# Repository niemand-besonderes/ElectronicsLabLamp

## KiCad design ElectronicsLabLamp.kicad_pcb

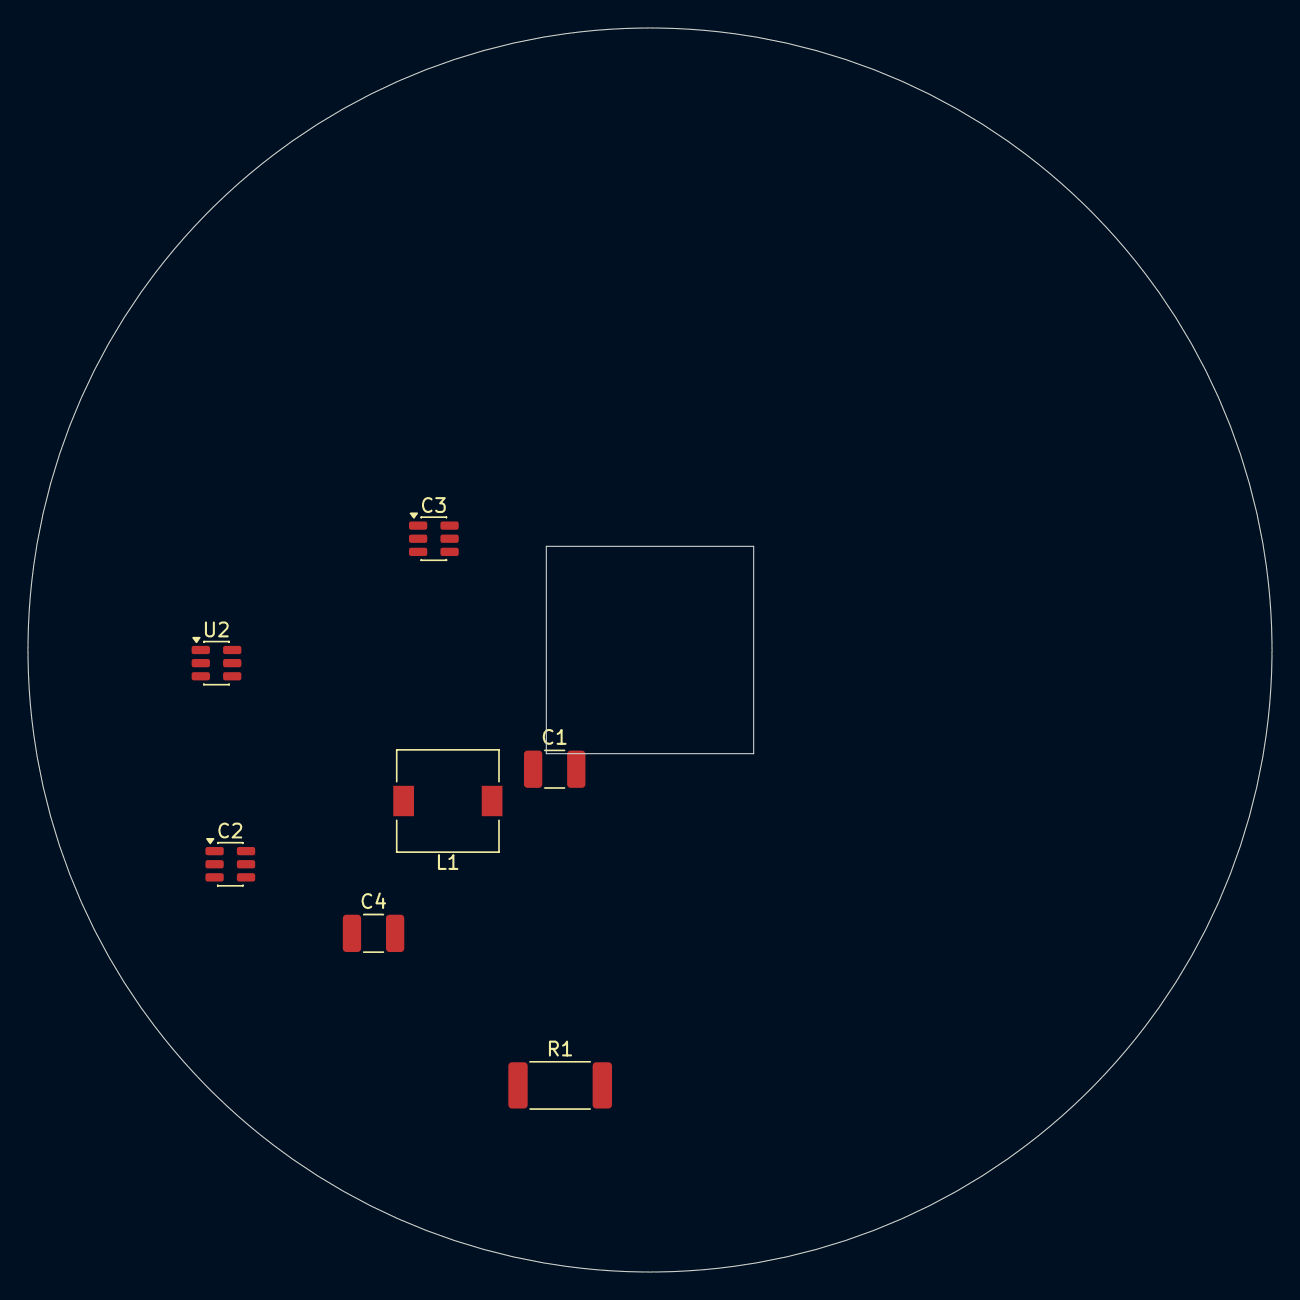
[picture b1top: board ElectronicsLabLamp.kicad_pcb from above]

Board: 2 copper layers, 90.0 x 90.0 mm, 7 parts (0 on the bottom side), 6 nets, no tracks yet.

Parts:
C1, C4: 10uF; C_1210_3225Metric_Pad1.33x2.70mm_HandSolder
C2, C3: 0.1uF; SOT-23-6
L1: 8.2uH; L_7.3x7.3_H4.5
R1: 120mR; R_2512_6332Metric_Pad1.40x3.35mm_HandSolder
U2: TPS92200D1DDC; SOT-23-6

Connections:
+12V: C1.1, C2.1, U2.4 (VIN)
GND: C1.2, C2.2, C4.2, R1.2, U2.3 (GND)
unnamed: C4.1, L1.2
unnamed: R1.1, U2.1 (FB)
unnamed: C3.2, L1.1, U2.6 (BOOT)
unnamed: C3.1, U2.5 (SW)
